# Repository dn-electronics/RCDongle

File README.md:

RCDongle
=========
Introduction
============
The RCDongle is a plug in USB device that decodes infrared signals.

Features
========
1. Reprogrammable USB enabled AT90USB162 microcontroller
2. ESD protection diode
3. TSOP352/4 IR receiver module with a centre frequency of either 30, 33, 36, 38, 40 or 56 kHz depending on the application.

Licence
=======
<p>This work is licensed under a <a href="http://www.creativecommons.org/licenses/by-sa/3.0" target="_blank">Creative Commons Attribution-ShareAlike 3.0 Unported License</a>

Schematic
=========

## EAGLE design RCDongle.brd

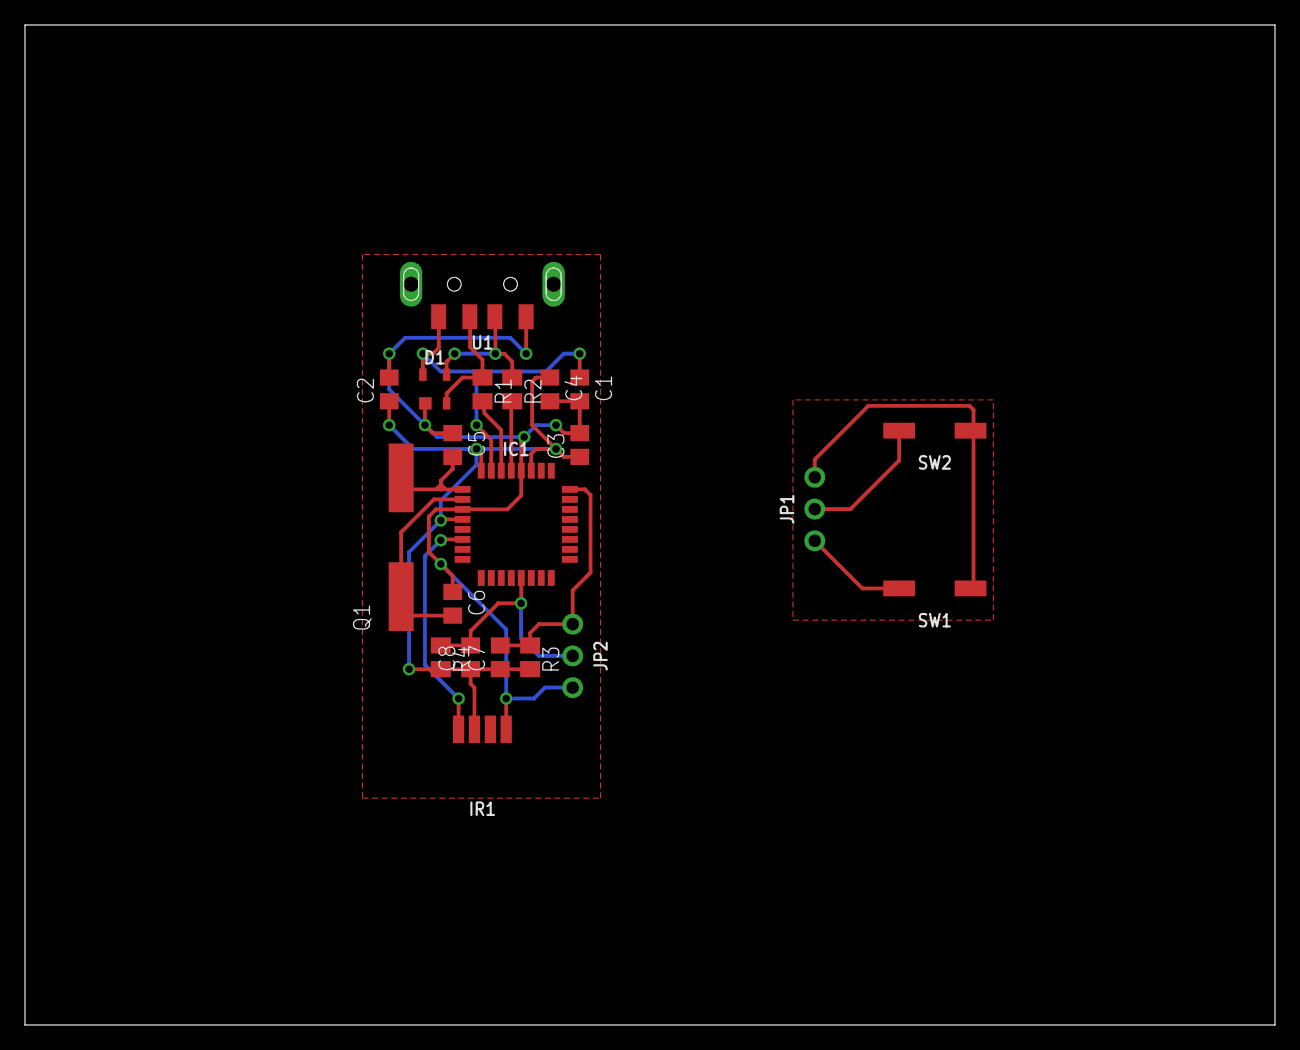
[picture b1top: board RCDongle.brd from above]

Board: 2 copper layers, 100.0 x 80.0 mm, 21 parts (0 on the bottom side), 15 nets.

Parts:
C1, C2, C3, C4: 100nF; C0805
C5, C6: 18pF; C0805
C7, C8: 220nF; C0805
D1: PRTR5V0U2X; P-SOT143BE
IC1: AT90USB162; P-TQFP32
IR1: TSOP35; P-TSOP35
JP1, JP2: P-1X03
Q1: 8MHz; CSM-7X-DU
R1, R2: 22R; M0805
R3, R4: 47K; M0805
SW1, SW2: P-SWITCH-SMT-DTSM31NV
U1: P-USB-TYPEA-PLUG

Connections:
GND: C1.2, C2.2, C3.2, C4.2, C5.1, C6.1, D1.1, IC1.3, IC1.28, IR1.1, JP2.3, U1.4
unnamed: C5.2, IC1.1, Q1.2
unnamed: C6.2, IC1.2, Q1.1
unnamed: IC1.30, R1.2
unnamed: IC1.29, R2.2
unnamed: JP1.1, SW1.2
unnamed: JP1.2, SW2.2
unnamed: D1.3, R2.1, U1.3
unnamed: D1.2, R1.1, U1.2
unnamed: C8.2, IC1.13, JP2.2, R4.1
unnamed: C1.1, D1.4, IC1.31, U1.1
unnamed: C7.2, IC1.24, JP2.1, R3.1
unnamed: JP1.3, SW1.1, SW2.1
unnamed: C2.1, C3.1, C4.1, C7.1, C8.1, IC1.4, IC1.27, IC1.32, IR1.3, R3.2, R4.2
unnamed: IC1.6, IR1.4
